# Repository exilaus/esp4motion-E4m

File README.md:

# esp4motion-E4m
killed

go to helping :
https://github.com/ryannining/karyacontroller

regards

old info.

This project want use D1 mini as basilar brain for Plotters lasercut cnc 3d printers.
currently in wip based from marginallyclever code portin on esp by Misan 

project currently managed by:
-Misan (Miguel sanchez)
-Exilaus (mauro manco)
-Darkberg (alex)

:) first preview set of board ordered....soon some news

Some info on board:
https://docs.google.com/presentation/d/1Ur_RV33AqiUAMNY1md2GBHKGxP4hxiyhX0XLN1OoxBo/edit?usp=sharing

First test of Misan
https://www.youtube.com/watch?v=iX7SKLwmQTw

For any info you can contact myself on G+ :) after test basic function on board need more coder :)

enjoy

Lib for arduino:

- https://github.com/tzapu/WiFiManager
- https://github.com/hibikiledo/Adafruit-MCP23017-Arduino-Library

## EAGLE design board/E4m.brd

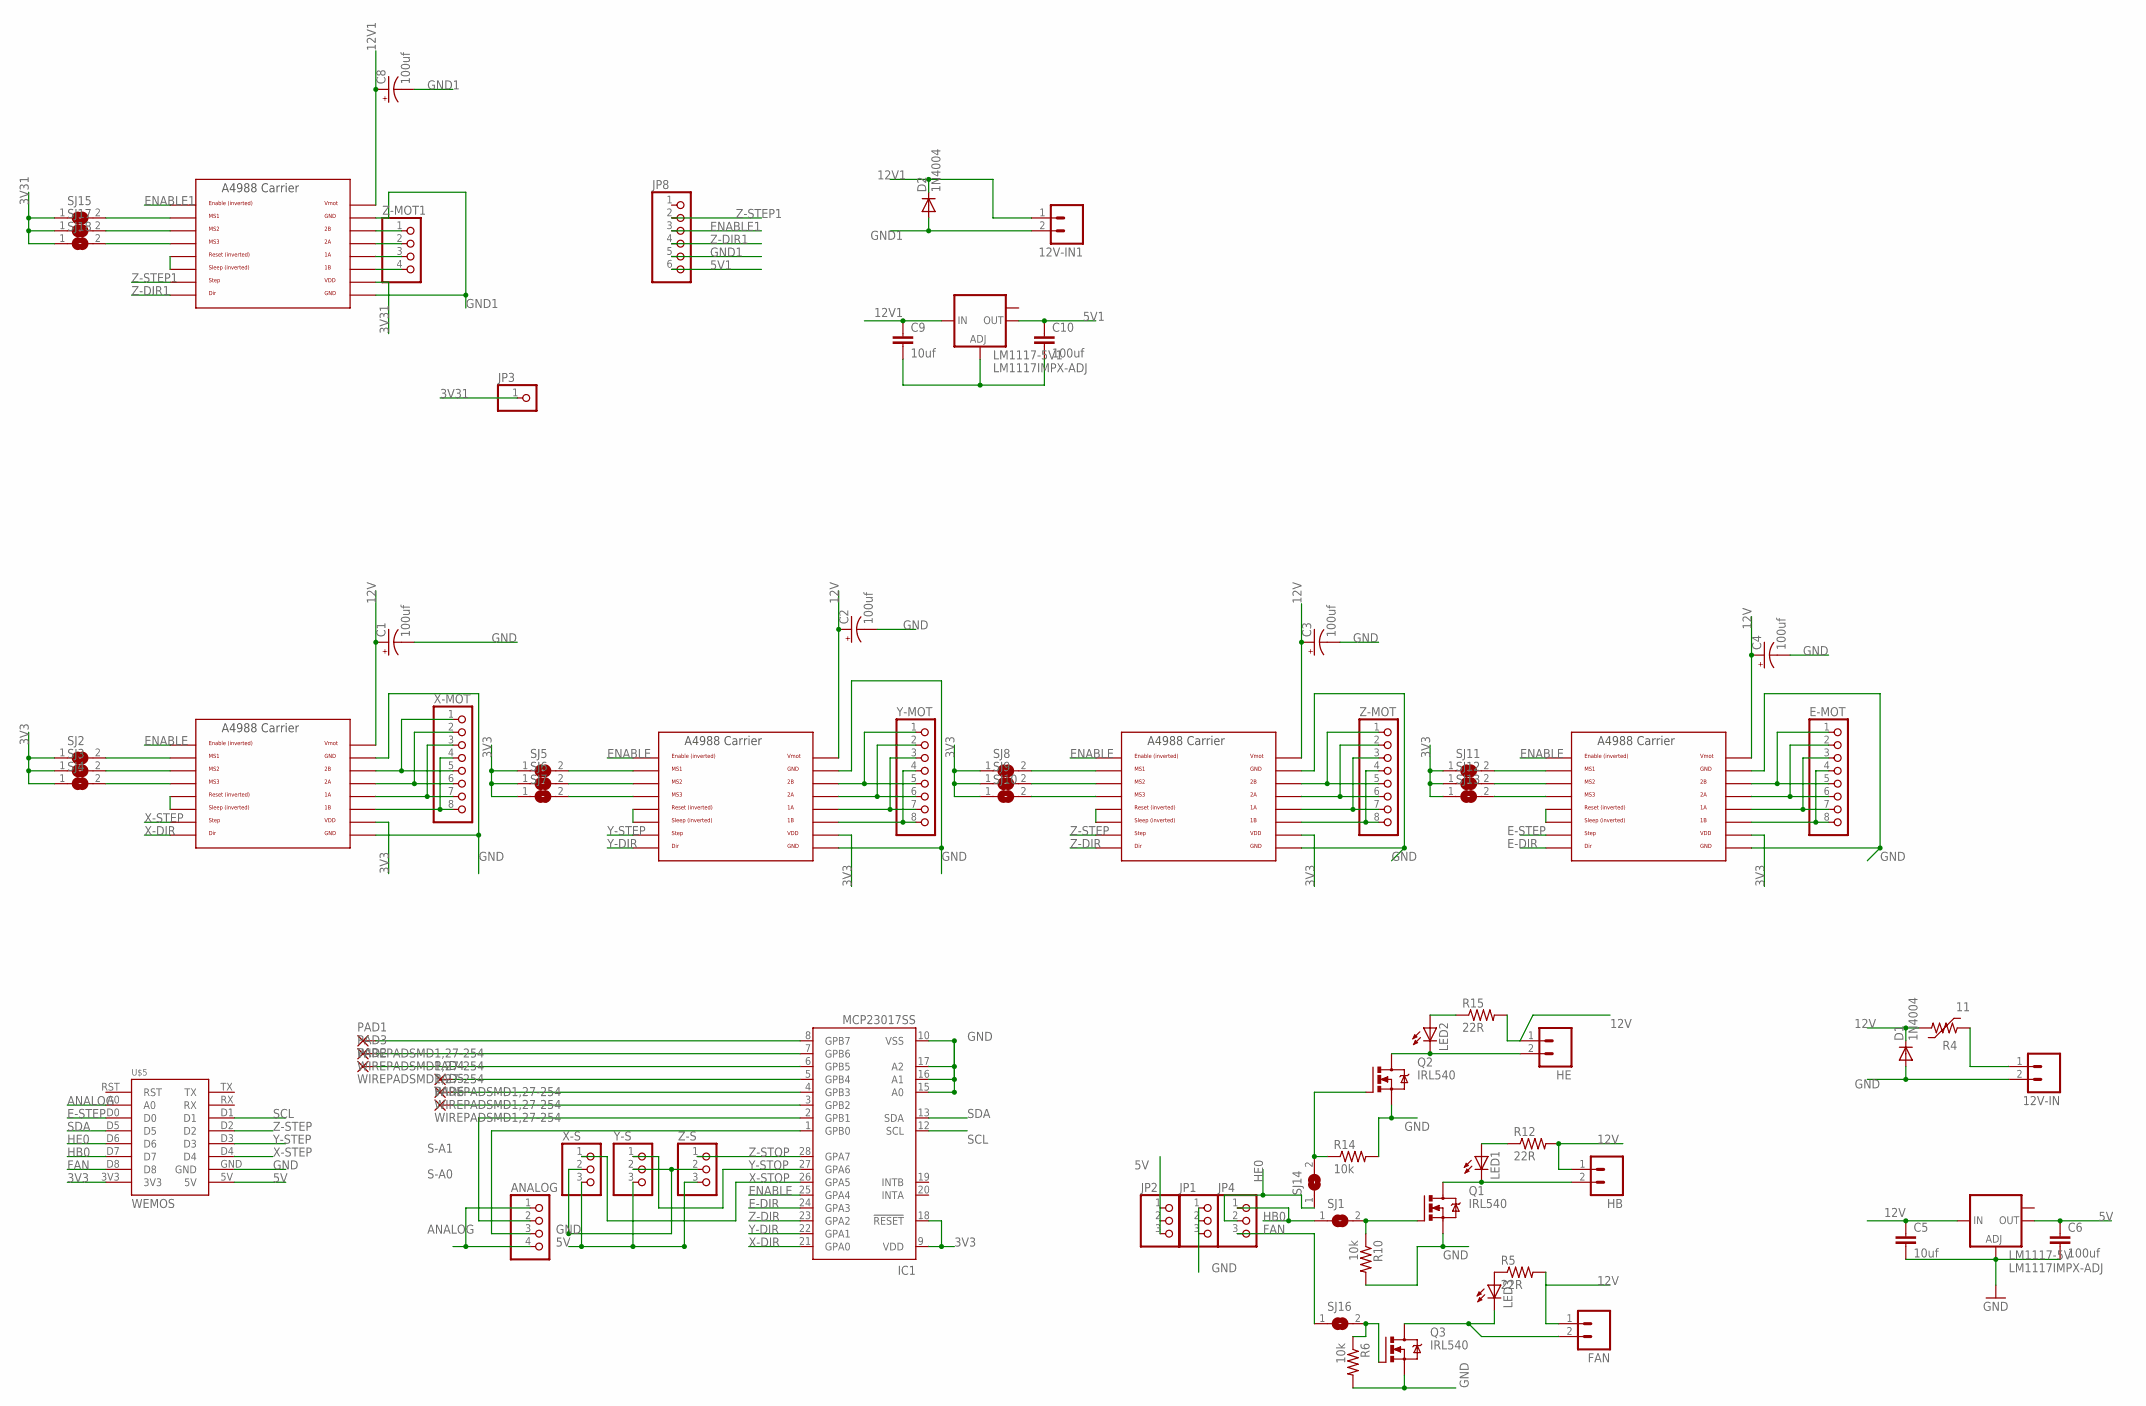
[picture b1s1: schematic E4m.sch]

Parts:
12V-IN, 12V-IN1: M02PTH; 1X02
ANALOG: PINHD-1X4; 1X04
C1, C2, C3, C4, C8: 100uf; 153CLV-0605
C5: 10uf; C0805
C6: 100uf; C0805
C9: 10uf; C0603
C10: 100uf; C0603
D1, D2: 1N4004; DO41-10
E-MOT: PINHD-1X8CLEANBIG; 1X08-CLEANBIG
FAN: M02PTH; 1X02
HB: M02PTH; 1X02
HE: M02PTH; 1X02
IC1: MCP23017SS; SSOP28
JP1, JP2, JP4: PINHD-1X3CB; 1X03-CLEANBIG
JP3: PINHD-1X1CB; 1X01-CLEANBIG
JP8: PINHD-1X6; 1X06
LED1, LED2, LED3: LEDCHIP-LED0805; CHIP-LED0805
LM1117-5V, LM1117-5V1: LM1117IMPX-ADJ; SOT223
PAD1, PAD2, PAD3, PAD4, PAD5, PAD6: WIREPADSMD1,27-254; SMD1,27-2,54
Q1, Q2, Q3: IRL540; TO220BV
R4: 11; PF-8.0
R5, R12, R15: 22R; R0805
R6, R10, R14: 10k; R0805
SJ1, SJ2, SJ3, SJ4, SJ5, SJ6, SJ7, SJ8, SJ9, SJ10, SJ11, SJ12, SJ13, SJ14, SJ15, SJ16, SJ17, SJ18: SJ
U$1, U$2, U$3, U$6, U$9: A4988BREAKOUT
U$5: WEMOS
X-MOT: PINHD-1X8CLEANBIG; 1X08-CLEANBIG
X-S: PINHD-1X3CB; 1X03-CLEANBIG
Y-MOT: PINHD-1X8CLEANBIG; 1X08-CLEANBIG
Y-S: PINHD-1X3CB; 1X03-CLEANBIG
Z-MOT: PINHD-1X8CLEANBIG; 1X08-CLEANBIG
Z-MOT1: PINHD-1X4; 1X04
Z-S: PINHD-1X3CB; 1X03-CLEANBIG

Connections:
3V3: IC1.9 (VDD), IC1.18 (!RESET), SJ2.1, SJ3.1, SJ4.1, SJ5.1, SJ6.1, SJ7.1, SJ8.1, SJ9.1, SJ10.1, SJ11.1, SJ12.1, SJ13.1, U$1.VDD, U$2.VDD, U$3.VDD, U$5.3V3, U$9.VDD
3V31: JP3.1, SJ15.1, SJ17.1, SJ18.1, U$6.VDD
5V: C6.1, JP2.1, JP2.2, JP2.3, LM1117-5V.2 (OUT), U$5.5V, X-S.3, Y-S.3, Z-S.3
5V1: C10.1, JP8.6, LM1117-5V1.2 (OUT)
12V: C1.+, C2.+, C3.+, C4.+, C5.1, D1.C, FAN.1, HB.1, HE.1, LM1117-5V.3 (IN), R4.2, R5.2, R12.2, R15.2, U$1.VMOT, U$2.VMOT, U$3.VMOT, U$9.VMOT
12V1: 12V-IN1.1, C8.+, C9.1, D2.C, LM1117-5V1.3 (IN), U$6.VMOT
ANALOG: ANALOG.1, ANALOG.4, U$5.A0
AUX2: IC1.8 (GPB7), PAD1.1
E-DIR: IC1.24 (GPA3), U$2.DIR
E-STEP: U$2.STEP, U$5.D0
ENABLE: IC1.25 (GPA4), U$1.EN, U$2.EN, U$3.EN, U$9.EN
ENABLE1: JP8.3, U$6.EN
FAN: JP4.3, SJ16.1, U$5.D8
GND: 12V-IN.2, C1.-, C2.-, C3.-, C4.-, C5.2, C6.2, D1.A, IC1.10 (VSS), IC1.15 (A0), IC1.16 (A1), IC1.17 (A2), JP1.1, JP1.2, JP1.3, LM1117-5V.1 (ADJ), Q1.S, Q2.S, Q3.S, R6.2, R10.2, R14.2, U$1.GND, U$1.GND@0 (GND), U$2.GND, U$2.GND@0 (GND), U$3.GND, U$3.GND@0 (GND), U$5.GND, U$9.GND, U$9.GND@0 (GND), X-S.2, Y-S.2, Z-S.2
GND1: 12V-IN1.2, C8.-, D2.A, JP8.5, U$6.GND, U$6.GND@0 (GND)
HB0: JP4.1, SJ1.1, U$5.D7
HE0: JP4.2, SJ14.1, U$5.D6
unnamed: LED3.A, R5.1
unnamed: IC1.7 (GPB6), PAD3.1
unnamed: SJ12.2, U$2.MS2
unnamed: U$2.RST, U$2.SLP (SLEEP)
unnamed: SJ13.2, U$2.MS3
unnamed: SJ11.2, U$2.MS1
unnamed: U$3.1B, Y-MOT.4, Y-MOT.8
unnamed: U$3.1A, Y-MOT.3, Y-MOT.7
unnamed: U$3.2A, Y-MOT.2, Y-MOT.6
unnamed: U$3.2B, Y-MOT.1, Y-MOT.5
unnamed: U$1.1B, X-MOT.4, X-MOT.8
unnamed: HB.2, LED1.C, Q1.D
unnamed: U$1.1A, X-MOT.3, X-MOT.7
unnamed: U$1.2A, X-MOT.2, X-MOT.6
unnamed: U$1.2B, X-MOT.1, X-MOT.5
unnamed: U$9.1B, Z-MOT.4, Z-MOT.8
unnamed: FAN.2, LED3.C, Q3.D
unnamed: IC1.3 (GPB2), PAD6.1
unnamed: U$9.1A, Z-MOT.3, Z-MOT.7
unnamed: IC1.6 (GPB5), PAD2.1
unnamed: IC1.5 (GPB4), PAD4.1
unnamed: Q2.G, R14.1, SJ14.2
unnamed: SJ3.2, U$1.MS2
unnamed: U$9.RST, U$9.SLP (SLEEP)
unnamed: IC1.4 (GPB3), PAD5.1
unnamed: Q3.G, R6.1, SJ16.2
unnamed: U$3.RST, U$3.SLP (SLEEP)
unnamed: U$1.RST, U$1.SLP (SLEEP)
unnamed: 12V-IN.1, R4.1
unnamed: SJ4.2, U$1.MS3
unnamed: SJ2.2, U$1.MS1
unnamed: SJ17.2, U$6.MS2
unnamed: SJ18.2, U$6.MS3
unnamed: SJ15.2, U$6.MS1
unnamed: U$6.2B, Z-MOT1.1
unnamed: U$6.2A, Z-MOT1.2
unnamed: U$6.1A, Z-MOT1.3
unnamed: U$6.1B, Z-MOT1.4
unnamed: U$6.RST, U$6.SLP (SLEEP)
unnamed: U$9.2A, Z-MOT.2, Z-MOT.6
unnamed: U$9.2B, Z-MOT.1, Z-MOT.5
unnamed: C9.2, C10.2, LM1117-5V1.1 (ADJ)
unnamed: E-MOT.4, E-MOT.8, U$2.1B
unnamed: E-MOT.3, E-MOT.7, U$2.1A
unnamed: LED1.A, R12.1
unnamed: E-MOT.2, E-MOT.6, U$2.2A
unnamed: SJ6.2, U$3.MS2
unnamed: HE.2, LED2.C, Q2.D
unnamed: SJ7.2, U$3.MS3
unnamed: SJ5.2, U$3.MS1
unnamed: E-MOT.1, E-MOT.5, U$2.2B
unnamed: SJ9.2, U$9.MS2
unnamed: LED2.A, R15.1
unnamed: SJ10.2, U$9.MS3
unnamed: SJ8.2, U$9.MS1
N$S4: Q1.G, R10.1, SJ1.2
S-A0: ANALOG.3, IC1.1 (GPB0)
S-A1: ANALOG.2, IC1.2 (GPB1)
SCL: IC1.12 (SCL), U$5.D1
SDA: IC1.13 (SDA), U$5.D5
X-DIR: IC1.21 (GPA0), U$1.DIR
X-STEP: U$1.STEP, U$5.D4
X-STOP: IC1.26 (GPA5), X-S.1
Y-DIR: IC1.22 (GPA1), U$3.DIR
Y-STEP: U$3.STEP, U$5.D3
Y-STOP: IC1.27 (GPA6), Y-S.1
Z-DIR: IC1.23 (GPA2), U$9.DIR
Z-DIR1: JP8.4, U$6.DIR
Z-STEP: U$5.D2, U$9.STEP
Z-STEP1: JP8.2, U$6.STEP
Z-STOP: IC1.28 (GPA7), Z-S.1

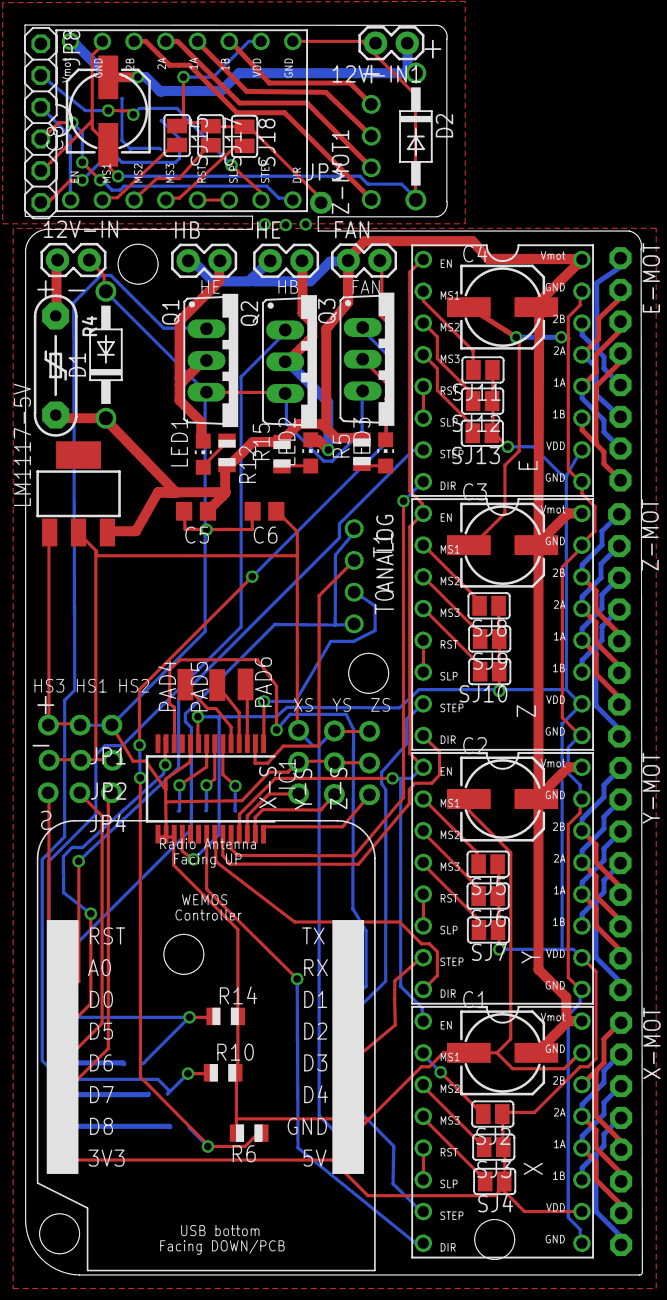
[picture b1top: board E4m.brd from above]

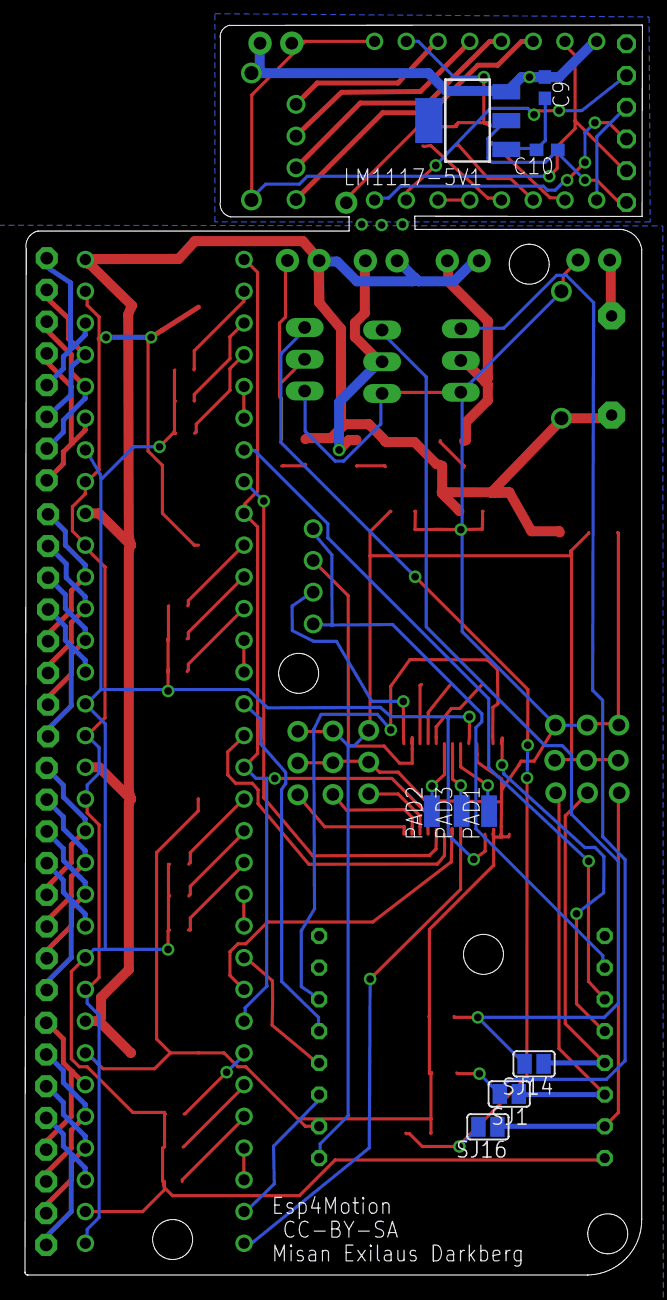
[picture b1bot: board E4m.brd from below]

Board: 2 copper layers, 49.4 x 100.1 mm, 76 parts (9 on the bottom side), 88 nets.

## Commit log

2016-10-17 :octocat: Added .gitattributes & .gitignore files
2016-10-17 before routing
    before routing
2016-10-17 routed
2016-10-18 final?
    mini4motion esp4motion
2016-10-18 Add files via upload
    reposition several elements for better routing
    routing done
    todo 1: fix 2 holes used for mounting/fixing the board
    todo 2: check all drc on file
2016-10-20 last verified
2016-10-21 ready...
2016-10-23 ops
    added servo output and panelized 100x100
2016-10-25 correct issue
    need re-route add all smd as 0805
2016-10-25 another update
2016-10-25 update git including software
2016-10-25 clean
2016-10-25 100% routed..... to clean before raster...
    yup
2016-10-25 again
    again
2016-10-25 dark clean and add raster
2016-10-25 reup
2016-10-25 clean clean clean
2016-10-25 update more and more :(
    agrrr
2016-10-25 again
2016-10-25 software update
    make something same marlin....
2016-10-25 check
2016-10-25 ok...issue on git..
2016-10-26 last...
    start panellization
2016-10-26 some fake code...
    studing https://github.com/iandouglas96/piPrint/tree/master/Server
2016-10-26 test
2016-10-27 add plotter configuration
    changed pin header for d1 pin...need add mcp23017
2016-10-28 porting plotter completed need test
2016-10-30 plotter ino update after test mpc23017
2016-10-31 homing xy
    basic homing
2016-11-16 uppete

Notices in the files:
board/E4m.brd:
CC-BY-SA
parts and their libraries:
polyswitch: Copyright (C) 2008, Bob Starr
